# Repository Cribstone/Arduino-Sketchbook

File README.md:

# Arduino-Sketchbook
My Arduino Sketchbook hosted and syncronized on Github.  Please note: Most sketches in this repo are in an incomplete state of development or are being used as templates for use in new sketches.  Feel free to make a pull request if you see something that you would like to use in your own project.
With the above caveats in consideration if you have any questions please feel free to open up a new issue- https://github.com/Cribstone/Arduino-Sketchbook/issues and I'll do my best to answer!

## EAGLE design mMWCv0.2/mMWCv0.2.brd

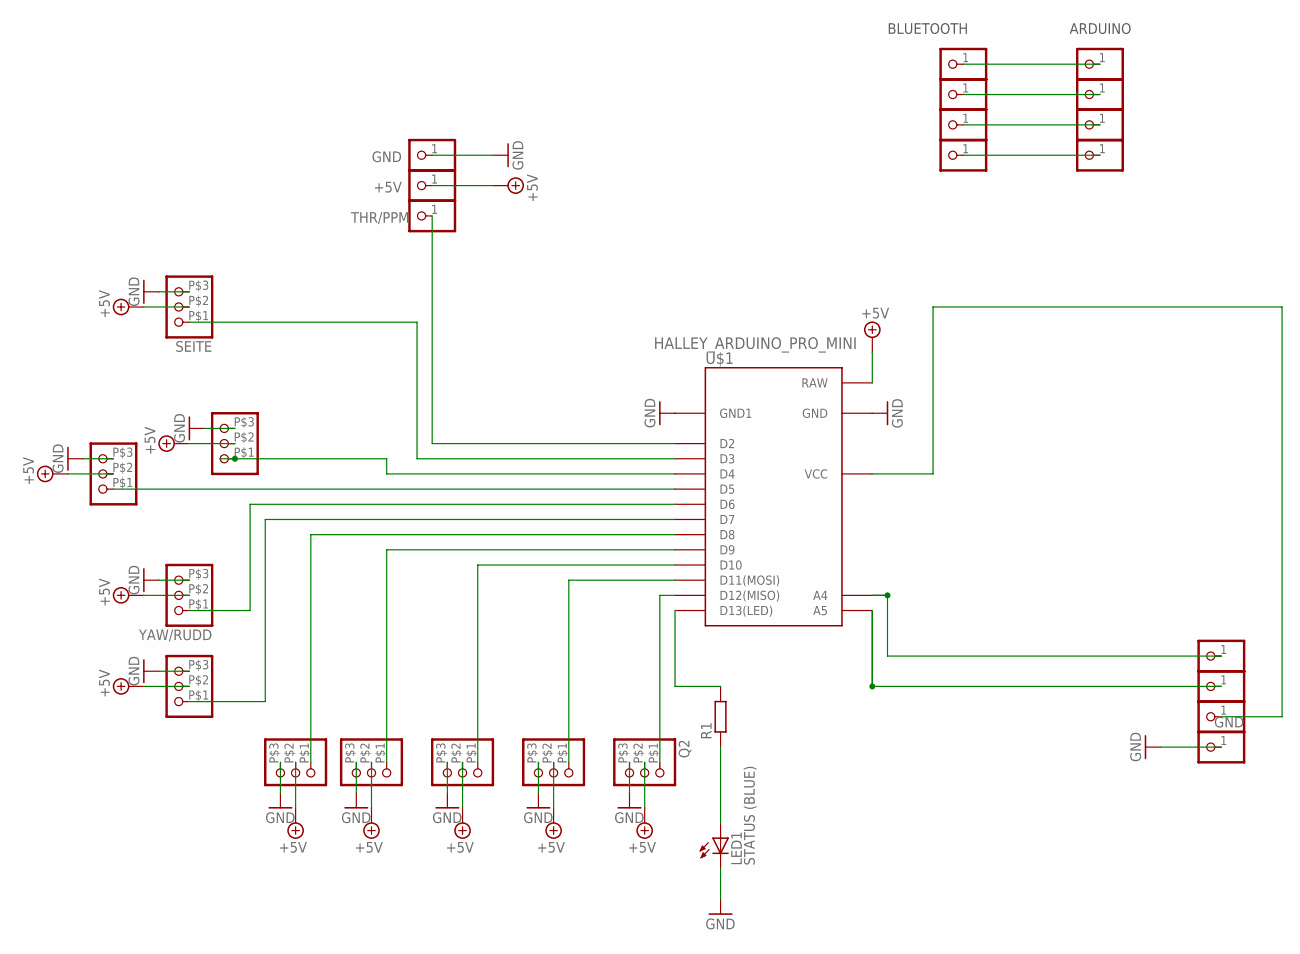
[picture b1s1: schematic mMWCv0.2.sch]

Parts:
5V: PINHD-1X1; 1X01
+5V: PINHD-1X1; 1X01
A4, A5: PINHD-1X1; 1X01
AIL: PINHEAD_PINHD-1X3; PINHEAD_1X03
ARD_GND: PINHD-1X1; 1X01
ARD_RX: PINHD-1X1; 1X01
ARD_TX: PINHD-1X1; 1X01
ARD_VCC: GND; 1X01
AUX2: PINHEAD_PINHD-1X3; PINHEAD_1X03
BT_GND: PINHD-1X1; 1X01
BT_RX: PINHD-1X1; 1X01
BT_TX: PINHD-1X1; 1X01
BT_VCC: GND; 1X01
ELE/PITCH: PINHEAD_PINHD-1X3; PINHEAD_1X03
GND: PINHD-1X1; 1X01
GND_: GND; 1X01
HÖHE: PINHEAD_PINHD-1X3; PINHEAD_1X03
LED1: STATUS (BLUE); CHIPLED_1206
MODE: PINHEAD_PINHD-1X3; PINHEAD_1X03
MOTOR: PINHEAD_PINHD-1X3; PINHEAD_1X03
Q1, Q2: PINHEAD_PINHD-1X3; PINHEAD_1X03
R1: R-EU_R1206; R1206
SEITE: PINHEAD_PINHD-1X3; PINHEAD_1X03
THR/PPM: PINHD-1X1; 1X01
U$1: HALLEY_ARDUINO_PRO_MINI
YAW/RUDD: PINHEAD_PINHD-1X3; PINHEAD_1X03

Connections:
+5V: +5V.1, AIL.P$2 (2), AUX2.P$2 (2), ELE/PITCH.P$2 (2), HÖHE.P$2 (2), MODE.P$2 (2), MOTOR.P$2 (2), Q1.P$2 (2), Q2.P$2 (2), SEITE.P$2 (2), U$1.RAW, YAW/RUDD.P$2 (2)
BT_ARD_GND: ARD_GND.1, BT_GND.1
BT_ARD_VCC: ARD_VCC.1, BT_VCC.1
GND: AIL.P$3 (3), AUX2.P$3 (3), ELE/PITCH.P$3 (3), GND.1, GND_.1, HÖHE.P$3 (3), LED1.C, MODE.P$3 (3), MOTOR.P$3 (3), Q1.P$3 (3), Q2.P$3 (3), SEITE.P$3 (3), U$1.GND (GND1), U$1.GND1 (GND), YAW/RUDD.P$3 (3)
unnamed: THR/PPM.1, U$1.D2
unnamed: AIL.P$1 (1), U$1.D4
unnamed: SEITE.P$1 (1), U$1.D3
unnamed: ELE/PITCH.P$1 (1), U$1.D5
unnamed: MODE.P$1 (1), U$1.D7
unnamed: Q2.P$1 (1), U$1.D12 (D12(MISO))
unnamed: AUX2.P$1 (1), U$1.D8
unnamed: A4.1, U$1.A4
unnamed: R1.2, U$1.D13 (D13(LED))
unnamed: U$1.D6, YAW/RUDD.P$1 (1)
unnamed: MOTOR.P$1 (1), U$1.D9
unnamed: HÖHE.P$1 (1), U$1.D10
unnamed: Q1.P$1 (1), U$1.D11 (D11(MOSI))
unnamed: LED1.A, R1.1
unnamed: 5V.1, U$1.VCC
unnamed: A5.1, U$1.A5
unnamed: ARD_RX.1, BT_TX.1
unnamed: ARD_TX.1, BT_RX.1

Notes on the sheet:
BLUETOOTH
ARDUINO

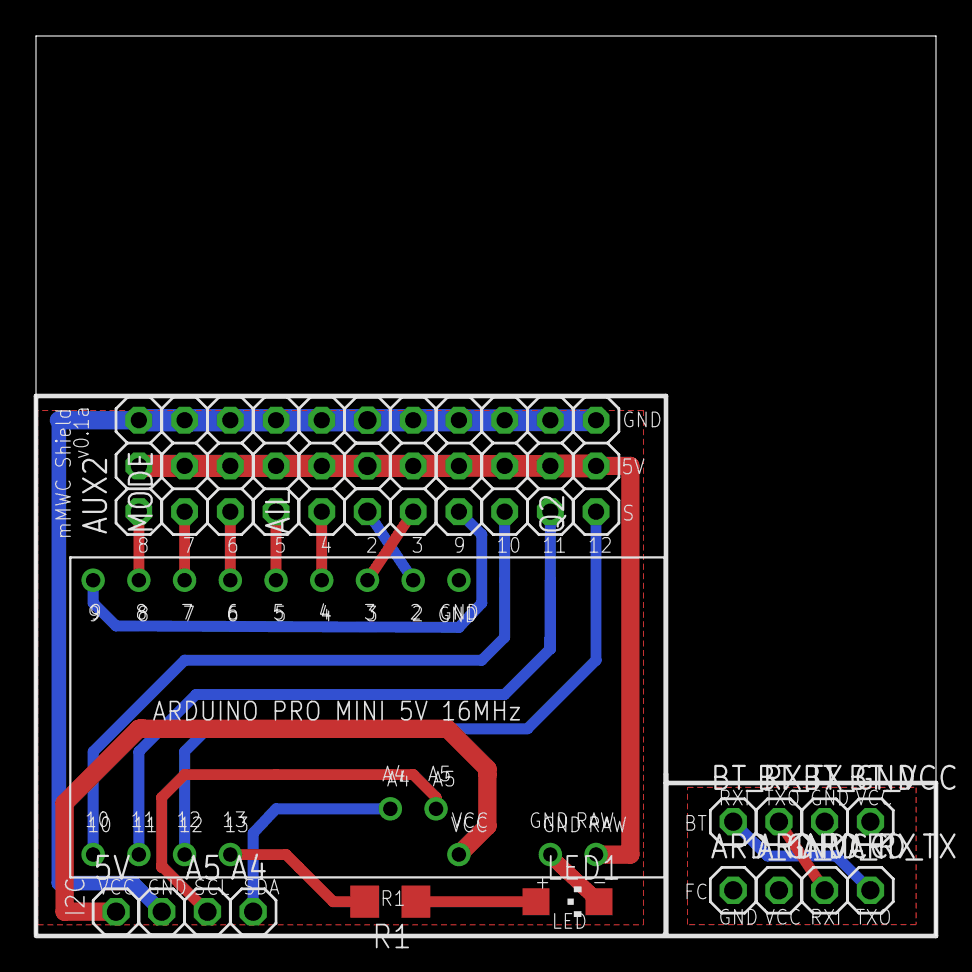
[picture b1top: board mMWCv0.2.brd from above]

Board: 2 copper layers, 50.0 x 50.0 mm, 28 parts (0 on the bottom side), 22 nets.

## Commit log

2013-07-07 Added Local Arduino Sketchbook
    Merged Ubuntu and Mac Sketch folders
2013-07-07 Added RSCamera.pde and SDFat Library
2013-07-28 Added ArduinoPhone
    Added Files for ArduinoPhone from
    https://github.com/yexiaobo-seeedstudio/ArduinoPhone
2015-11-18 Added note about sketchbook purpose
2015-11-18 Merged latest sketchbook and cleaned up some outdated libraries.
2015-11-18 Added Adafruit IO examples
2015-11-19 Added LidarLite Sketches
    Initial experiments with LidarLite for distance measurement and point
    cloud mapping.
2015-11-19 Added alternate i2C Library for LidarLite
2015-11-22 scrubbed
2015-11-22 Added Mysensors library1.5 and other automatic updates.
2015-11-29 Added new Esp files
2015-11-29 Cleaned up zip packages and orphaned sketches
2015-11-29 Added wifipixel sketches unmodified
2015-11-30 Updated Libraries and added vanilla MQTT Button sketch
2015-11-30 Added UartDriven Branch of NeopixelBus Library
2015-11-30 Added wifipixels repo as library and removed examples from sketch folder
2015-12-01 ID planetarium sketches
2015-12-03 Added note about submitting questions to gh-issues
2015-12-06 Added first experiments with ESP8266
2015-12-27 New RotaryEncodersketches
2015-12-29 Added modified RGBDimmer and library updates
2015-12-29 Removed servo library ref on colorwheel sketch
2016-04-23 Auto-Updates for libraries circa Arduino 1.6.8 and manually update to EReader library.
2016-04-23 Updated and Changed AlamodeEPD folder to EPD. Added EReader as standalone library.
